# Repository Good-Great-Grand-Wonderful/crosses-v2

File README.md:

A modular ergonomic columar staggered keyboard that's available in 36, 42, and 54 key layouts. Created by Good Great Grand Wonderful LLC. 

Made with a precise trackball sensor. Eliminating the need to have another pointing device, everything is within reach.

Available at http://ergokeyboards.com

### Features

- Matrix with a thumb cluster that works better with our opposable thumbs!
- Advanced 4 layer PCB with built in NRF52840 improves stability, and drastically simplifies soldering
- Main matrix layouts of: 3x5, 3x6, and 4x6
- Kailh Choc hotswap sockets, so you can explore and find your perfect switch
- Dual trackballs

### Documentation
[Build guides, firmware help, and trackball tuning](https://wiki.ergokeyboards.com)

### Firmware
[Releases](https://github.com/Good-Great-Grand-Wonderful/crosses-v2/releases)

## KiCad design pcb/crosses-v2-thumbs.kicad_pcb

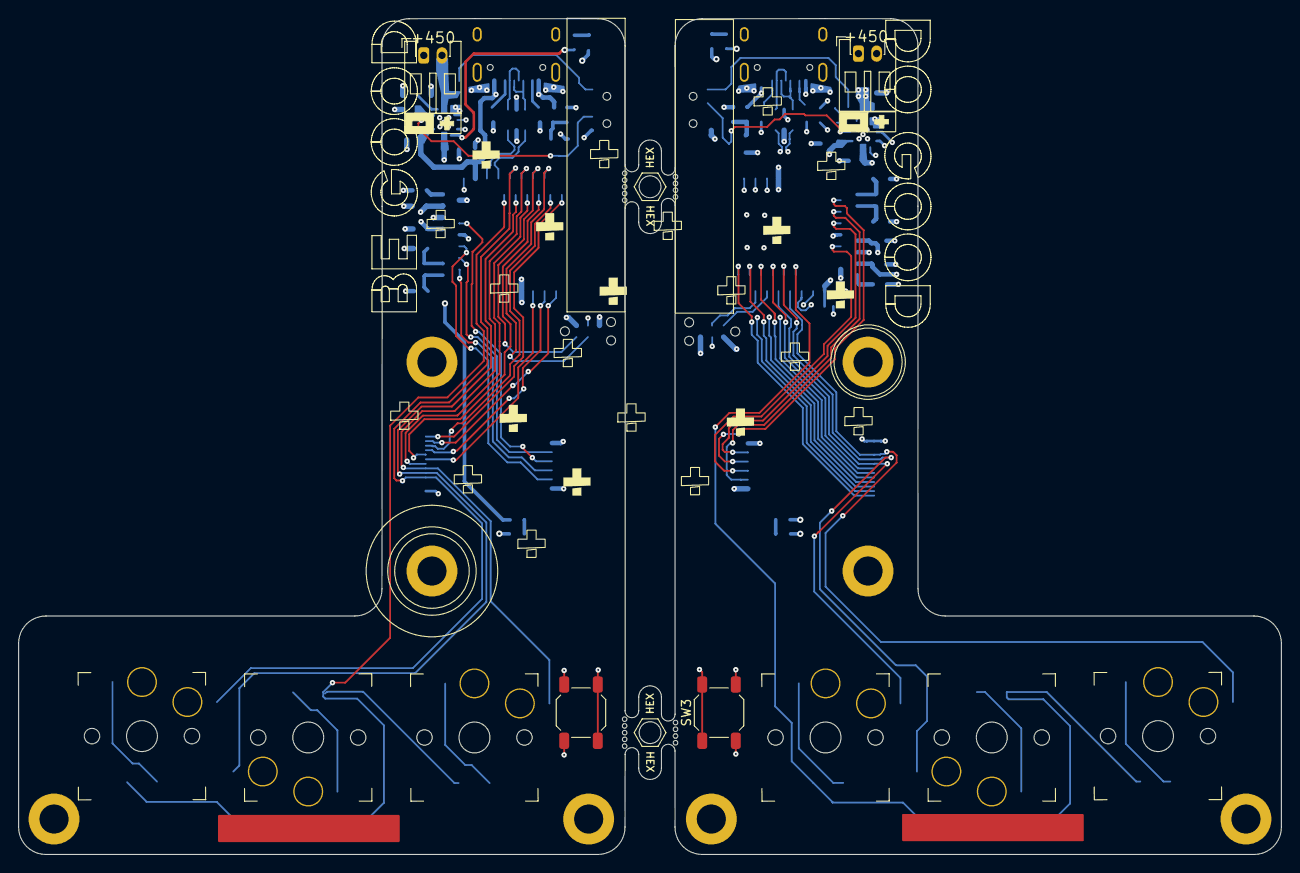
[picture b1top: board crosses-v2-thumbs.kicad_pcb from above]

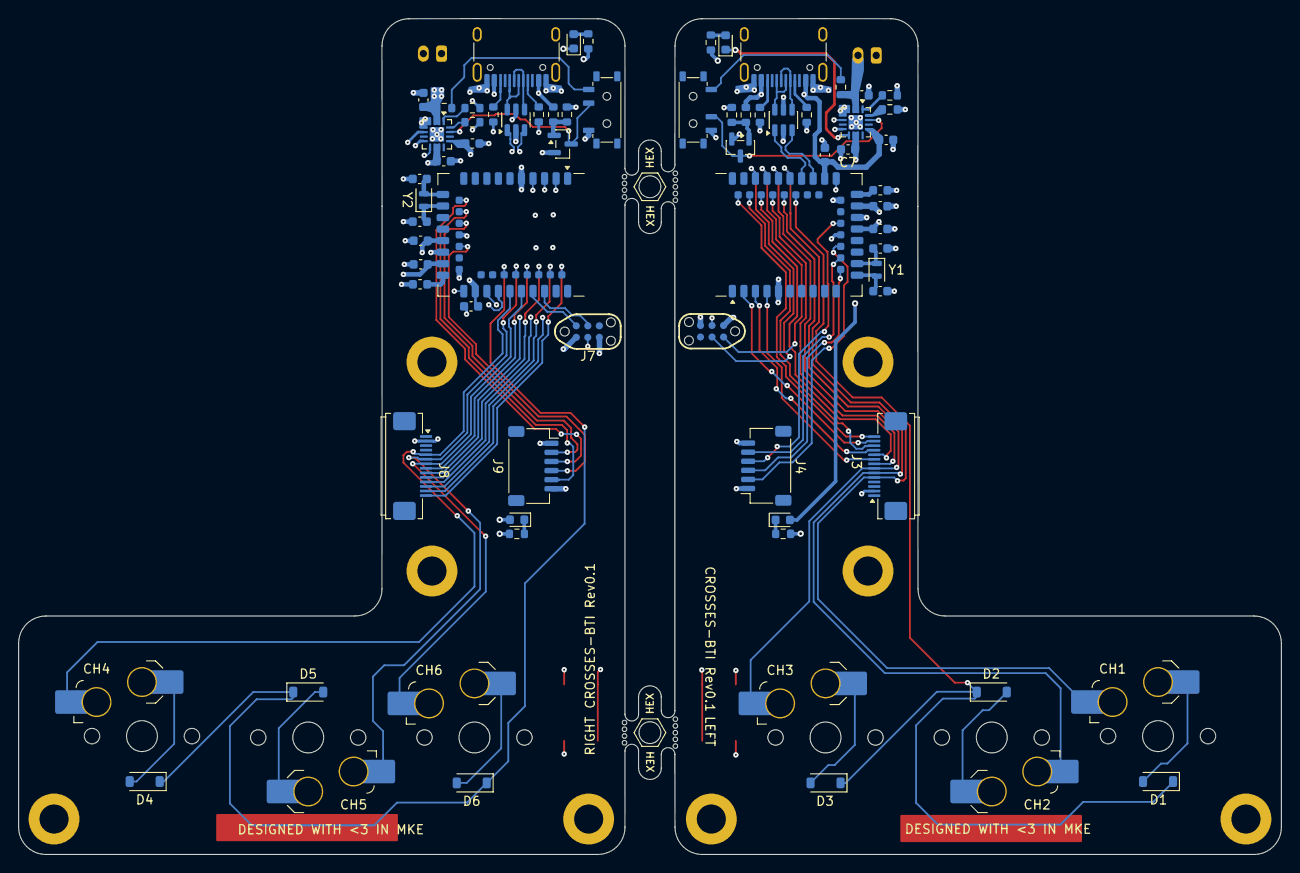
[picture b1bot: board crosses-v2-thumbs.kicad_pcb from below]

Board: 4 copper layers, 139.0 x 92.0 mm, 86 parts (76 on the bottom side), 83 nets.

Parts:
C1, C2, C9, C10: 12p; C_0603_1608Metric
C3, C11: 1u; C_0603_1608Metric
C4, C5, C6, C7, C8, C12, C13, C14, C15, C16: 4u7; C_0603_1608Metric
CH1, CH2, CH3, CH4, CH5, CH6: CPG135001S30; SW_choc_v1_HS_CPG135001S30_1u
D1, D2, D3, D4, D5, D6: 1N4148; D_SOD-123
D7, D8: LED; LED_0603_1608Metric
H1, H1#2, H2, H2#2, H3, H3#2, H3#3, H3#4: MountingHole; MountingHole_3.2mm_M3_DIN965_Pad
J1, J6: HRO_TYPE-C-31-M-14; USB_C_Receptacle_HRO_TYPE-C-31-M-12
J2, J7: TC2030_SWD; CON_TC2030_outlined
J3, J8: Conn_01x14_Pin; XUNPU_FPC-05F-14PH20_1x14-1MP_P0.5mm_Horizontal
J4, J9: SM06B-SRSS-TB(LF)(SN); JST_SH_SM06B-SRSS-TB_1x06-1MP_P1.00mm_Horizontal
J5, J10: Battery; TE_440055-2_1x02_P2.00mm_Horizontal
L1, L2: 10 uH; L_0603_1608Metric
LED1, LED2: orange; LED_0603_1608Metric
MB5, MB5#2: 5.5mm; mousebites_5p5mm_easysnap
Q1, Q2: 2N7002; SOT-23
R1, R2, R9, R10: 5k1; R_0603_1608Metric
R3, R11: 100k; R_0603_1608Metric
R4, R12: 100R; R_0603_1608Metric
R5, R6, R7, R13, R14, R15: 10k; R_0603_1608Metric
R8, R16: 3k9; R_0603_1608Metric
R17, R18: 1k; R_0603_1608Metric
SW1, SW3: RST; SW_SPST_SKQG_WithStem
SW2, SW4: PWR; SW_MSK12C02-HB
U1, U4: USBLC6-2SC6; SOT-23-6
U2, U5: nRF52840_E73-2G4M08S1C
U3, U6: BQ24075; VQFN-16-1EP_3x3mm_P0.5mm_EP1.6x1.6mm
Y1, Y2: 32.768 KHz; Crystal_SMD_2012-2Pin_2.0x1.2mm

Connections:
3V3_SPI: C3.1, C11.1, J2.1 (VCC), J4.6, J7.1 (VCC), J9.6, L1.2, L2.2, U2.19 (VDD), U5.19 (VDD)
+5V: C4.1, C6.1, C12.1, C14.1, J1.A4 (VBUS), J1.A9 (VBUS), J1.B4 (VBUS), J1.B9 (VBUS), J6.A4 (VBUS), J6.A9 (VBUS), J6.B4 (VBUS), J6.B9 (VBUS), R4.1, R12.1, U1.5 (VBUS), U2.27 (VBUS), U3.13 (IN), U4.5 (VBUS), U5.27 (VBUS), U6.13 (IN)
+BATT: C8.1, C16.1, J5.2, J10.2, R3.2, R11.2, U3.2 (BAT), U3.3 (BAT), U6.2 (BAT), U6.3 (BAT)
+VSW_L: C5.1, C7.1, C13.1, C15.1, R5.1, R13.1, U2.23 (VDDH), U3.6 (EN1), U3.10 (OUT), U3.11 (OUT), U5.23 (VDDH), U6.6 (EN1), U6.10 (OUT), U6.11 (OUT)
/LeftThumb/COL0: J3.13, U2.2 (P1.10)
/LeftThumb/COL1: J3.9, U2.4 (P0.28/AIN4)
/LeftThumb/COL2: J3.8, U2.36 (P1.00)
/LeftThumb/COL3: CH1.1, J3.5, U2.33 (P0.13)
/LeftThumb/COL4: CH2.1, J3.6, U2.34 (P0.22)
/LeftThumb/COL5: CH3.1, J3.7, U2.35 (P0.24)
/LeftThumb/DCCH: L1.1, U2.25 (DCCH)
/LeftThumb/P0.06_SCLK: J4.5, U2.14 (P0.06)
/LeftThumb/P0.08_NCS: J4.2, U2.16 (P0.08)
/LeftThumb/P0.12_MOTION: J4.4, U2.20 (P0.12)
/LeftThumb/P0.26_SDIO: J4.3, U2.12 (P0.26)
/LeftThumb/ROW0: J3.14, U2.42 (P1.06)
/LeftThumb/ROW1: J3.10, U2.38 (P1.02)
/LeftThumb/ROW2: J3.11, U2.3 (P0.03/AIN1)
/LeftThumb/ROW3: J3.12, U2.40 (P1.04)
/LeftThumb/ROW4: D1.1 (K), D2.1 (K), D3.1 (K), U2.32 (P0.20)
/LeftThumb/RST: J2.3 (~RST), SW1.1, U2.26 (P0.18/~RESET)
/LeftThumb/STATUS_LED: D8.2 (A), U2.18 (P0.04/AIN2)
/LeftThumb/SWDCLK: J2.4 (SWCLK), U2.39 (SWDCLK)
/LeftThumb/SWDIO: J2.2 (SWDIO), U2.37 (SWDIO)
/LeftThumb/SYSOFF: Q1.3 (D), SW2.2 (B), U3.15 (SYSOFF)
/LeftThumb/USB_CONN_D+: J1.A6 (D+), J1.B6 (D+), U1.6 (I/O1)
/LeftThumb/USB_CONN_D-: J1.A7 (D-), J1.B7 (D-), U1.4 (I/O2)
/LeftThumb/USB_D+: U1.1 (I/O1), U2.31 (D+)
/LeftThumb/USB_D-: U1.3 (I/O2), U2.29 (D-)
/RightThumb/COL0: J8.13, U5.2 (P1.10)
/RightThumb/COL1: J8.9, U5.4 (P0.28/AIN4)
/RightThumb/COL2: J8.8, U5.36 (P1.00)
/RightThumb/COL3: CH4.1, J8.5, U5.33 (P0.13)
/RightThumb/COL4: CH5.1, J8.6, U5.34 (P0.22)
/RightThumb/COL5: CH6.1, J8.7, U5.35 (P0.24)
/RightThumb/DCCH: L2.1, U5.25 (DCCH)
/RightThumb/P0.06_SCLK: J9.5, U5.14 (P0.06)
/RightThumb/P0.08_NCS: J9.2, U5.16 (P0.08)
/RightThumb/P0.12_MOTION: J9.4, U5.20 (P0.12)
/RightThumb/P0.26_SDIO: J9.3, U5.12 (P0.26)
/RightThumb/ROW0: J8.14, U5.42 (P1.06)
/RightThumb/ROW1: J8.10, U5.38 (P1.02)
/RightThumb/ROW2: J8.11, U5.3 (P0.03/AIN1)
/RightThumb/ROW3: J8.12, U5.40 (P1.04)
/RightThumb/ROW4: D4.1 (K), D5.1 (K), D6.1 (K), U5.32 (P0.20)
/RightThumb/RST: J7.3 (~RST), SW3.1, U5.26 (P0.18/~RESET)
/RightThumb/STATUS_LED: D7.2 (A), U5.18 (P0.04/AIN2)
/RightThumb/SWDCLK: J7.4 (SWCLK), U5.39 (SWDCLK)
/RightThumb/SWDIO: J7.2 (SWDIO), U5.37 (SWDIO)
/RightThumb/SYSOFF: Q2.3 (D), SW4.2 (B), U6.15 (SYSOFF)
/RightThumb/USB_CONN_D+: J6.A6 (D+), J6.B6 (D+), U4.6 (I/O1)
/RightThumb/USB_CONN_D-: J6.A7 (D-), J6.B7 (D-), U4.4 (I/O2)
/RightThumb/USB_D+: U4.1 (I/O1), U5.31 (D+)
/RightThumb/USB_D-: U4.3 (I/O2), U5.29 (D-)
GND: C1.2, C2.2, C3.2, C4.2, C5.2, C6.2, C7.2, C8.2, C9.2, C10.2, C11.2, C12.2, C13.2, C14.2, C15.2, C16.2, J1.A1 (GND), J1.A12 (GND), J1.B1 (GND), J1.B12 (GND), J2.5 (GND), J3.2, J4.1, J5.1, J6.A1 (GND), J6.A12 (GND), J6.B1 (GND), J6.B12 (GND), J7.5 (GND), J8.2, J9.1, J10.1, Q1.2 (S), Q2.2 (S), R1.1, R2.1, R6.2, R7.2, R8.2, R9.1, R10.1, R14.2, R15.2, R16.2, R17.2, R18.2, SW1.2, SW2.3 (C), SW3.2, SW4.1 (A), U1.2 (GND), U2.5 (GND), U2.21 (GND), U2.24 (GND), U3.4 (~CE), U3.5 (EN2), U3.8 (VSS), U3.17 (VSS), U4.2 (GND), U5.5 (GND), U5.21 (GND), U5.24 (GND), U6.4 (~CE), U6.5 (EN2), U6.8 (VSS), U6.17 (VSS)
unnamed: CH1.2, D1.2 (A)
unnamed: CH2.2, D2.2 (A)
unnamed: CH3.2, D3.2 (A)
unnamed: CH4.2, D4.2 (A)
unnamed: CH5.2, D5.2 (A)
unnamed: CH6.2, D6.2 (A)
unnamed: D7.1 (K), R17.1
unnamed: D8.1 (K), R18.1
unnamed: J1.A5 (CC1), R2.2
unnamed: J1.B5 (CC2), R1.2
unnamed: J6.A5 (CC1), R10.2
unnamed: J6.B5 (CC2), R9.2
unnamed: LED1.2 (A), R5.2
unnamed: LED1.1 (K), U3.9 (~CHG)
unnamed: LED2.2 (A), R13.2
unnamed: LED2.1 (K), U6.9 (~CHG)
unnamed: Q1.1 (G), R4.2, R6.1
unnamed: Q2.1 (G), R12.2, R14.1
unnamed: R3.1, SW2.1 (A)
unnamed: R11.1, SW4.3 (C)
unnamed: C1.1, U2.11 (P0.00/XL1), Y1.2
unnamed: C2.1, U2.13 (P0.01/XL2), Y1.1
unnamed: R8.1, U3.16 (ISET)
unnamed: R7.1, U3.1 (TS)
unnamed: C9.1, U5.11 (P0.00/XL1), Y2.2
unnamed: C10.1, U5.13 (P0.01/XL2), Y2.1
unnamed: R16.1, U6.16 (ISET)
unnamed: R15.1, U6.1 (TS)
